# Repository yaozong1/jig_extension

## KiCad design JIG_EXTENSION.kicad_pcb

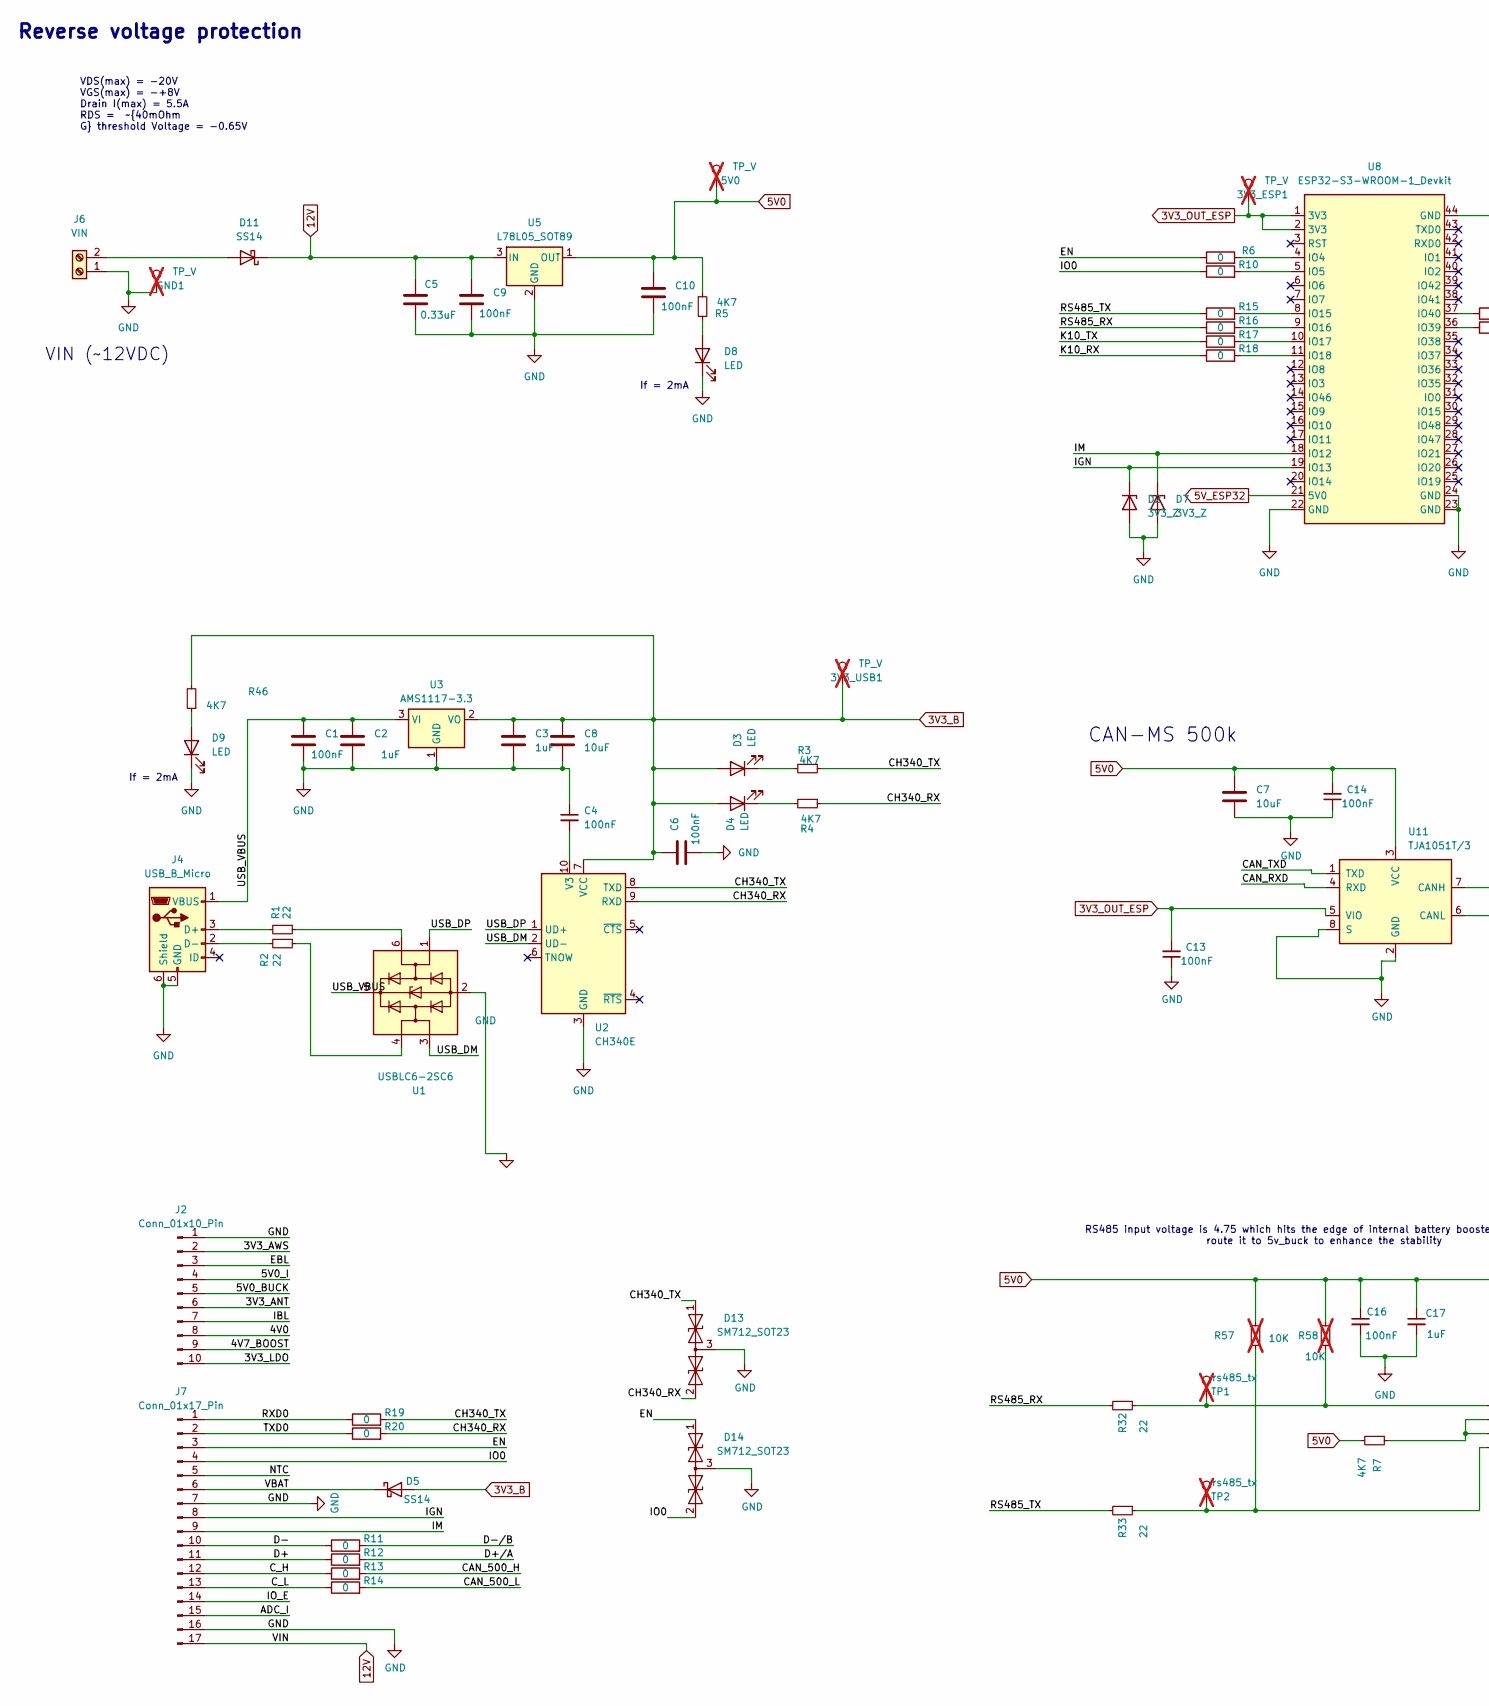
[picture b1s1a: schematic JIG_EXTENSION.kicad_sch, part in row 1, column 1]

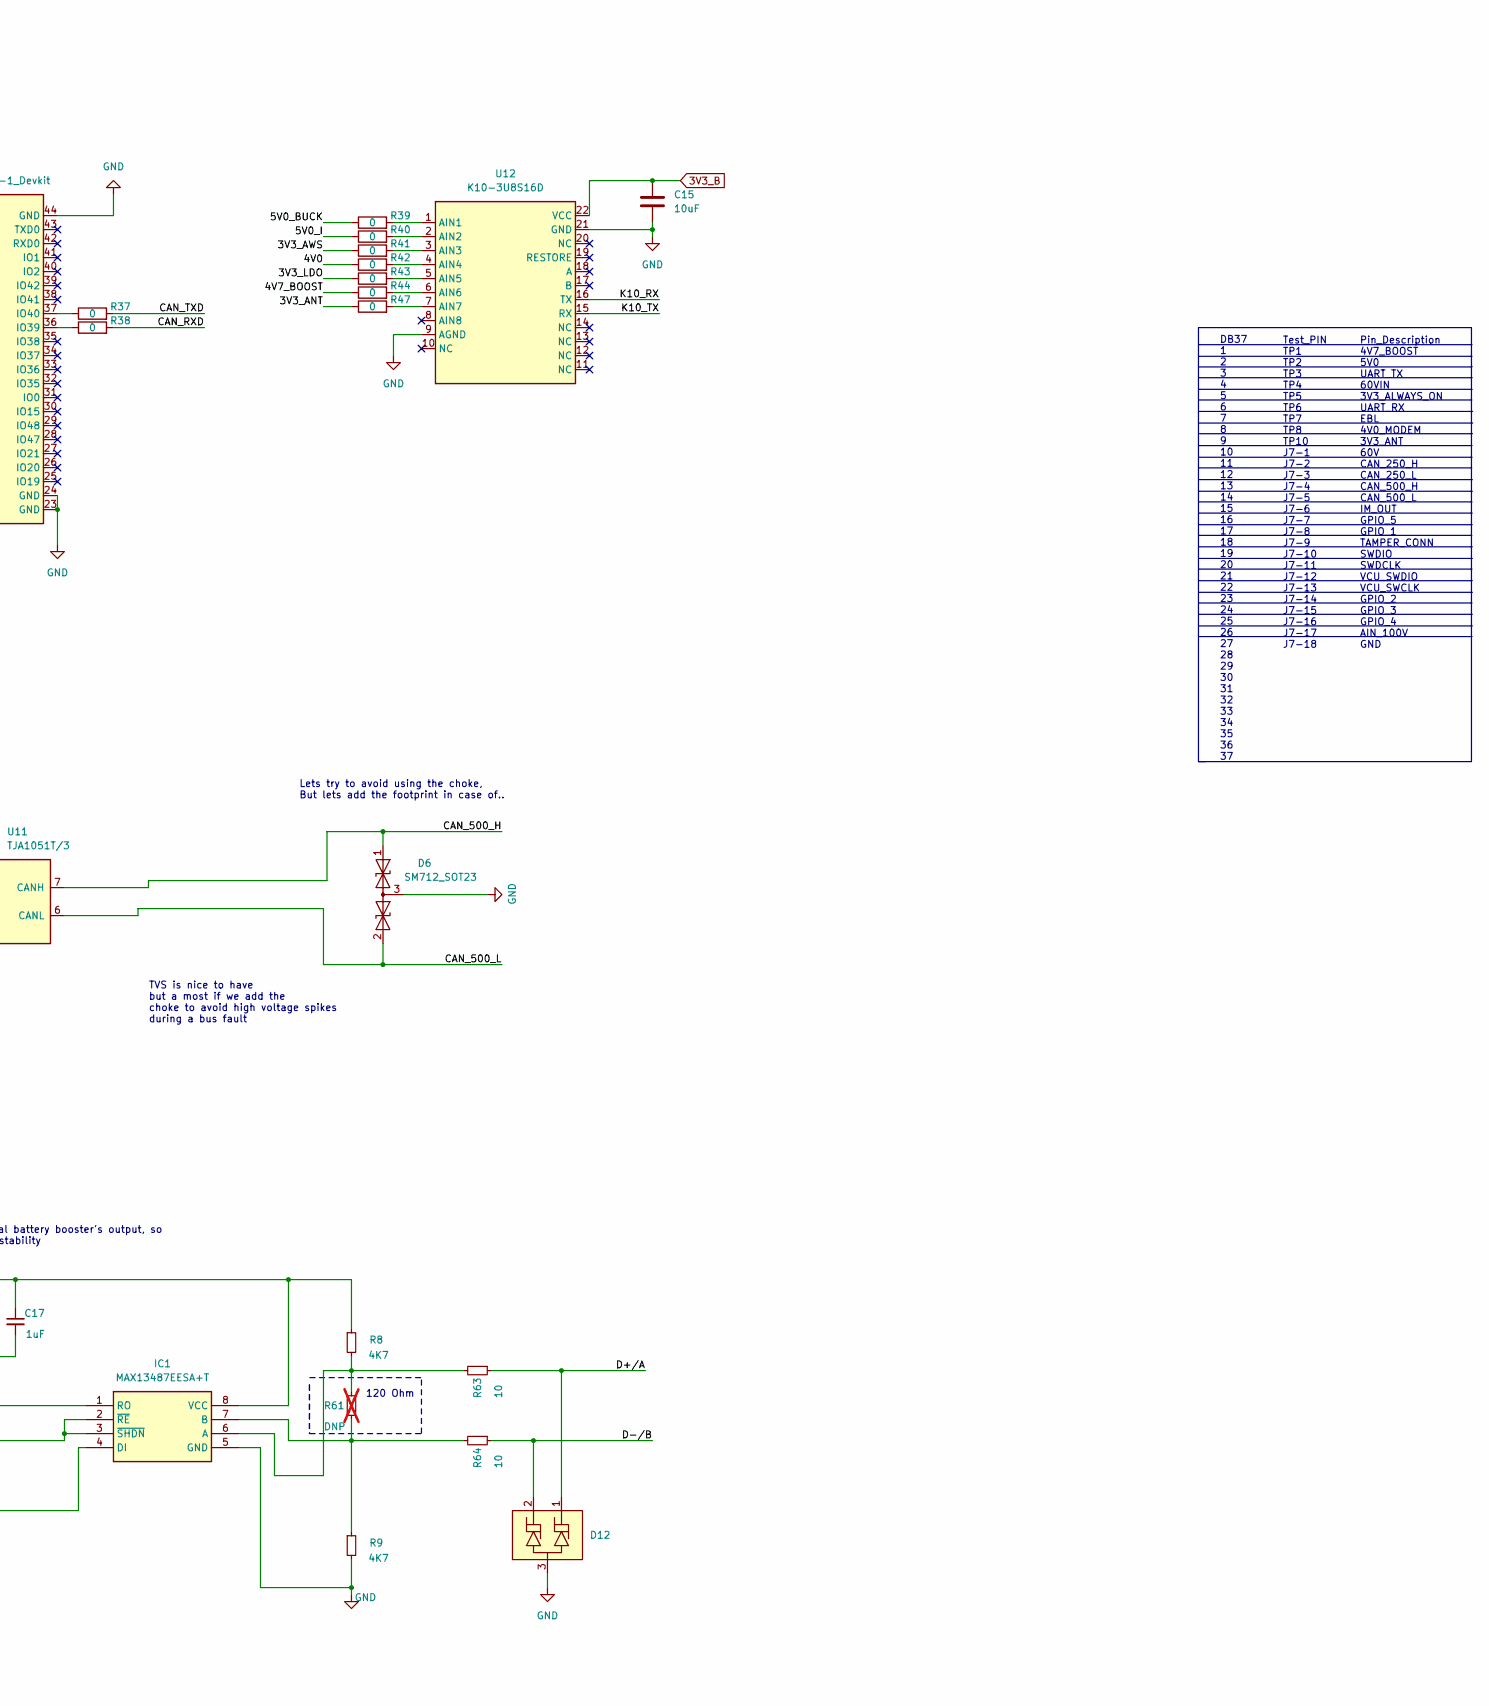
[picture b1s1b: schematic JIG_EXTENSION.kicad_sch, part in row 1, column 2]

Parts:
3V3_ESP1, 3V3_USB1, 5V0: TP_V; TestPoint_Pad_D1.0mm; MPN #N/A; LCSC Part #N/A; not fitted
C1, C4, C6, C9, C10, C13, C14, C16: 100nF; C_0603_1608Metric; MPN CC0603KRX7R9BB104; LCSC Part C14663
C2, C3, C17: 1uF; C_0603_1608Metric; MPN CL10A105KB8NNNC; LCSC Part C15849
C5: 0.33uF; C_0805_2012Metric; MPN 0805B334K500NT; LCSC Part C1740
C7, C8, C15: 10uF; C_0603_1608Metric; MPN CL10A106MA8NRNC; LCSC Part C96446
D2, D7: 3V3_Z; D_SOD-323; MPN BZT52C3V3S; LCSC Part C19077437
D3, D4, D8, D9: LED; LED_0603_1608Metric; MPN KT-0603R; LCSC Part C2286
D5, D11: SS14; D_SMA; MPN SS14; LCSC Part C2480
D6, D13, D14: SM712_SOT23; SOT-323_SC-70; MPN ESDCAN03-2BWY; LCSC Part C1973833
D12: PESD8V0L2BT-N; SOT-23; MPN PESD8V0L2BT-N; LCSC Part C316022
GND1: TP_V; TestPoint_Pad_D1.0mm; MPN #N/A; LCSC Part #N/A; not fitted
IC1: MAX13487EESA+T; SOIC127P600X175-8N; MPN MAX13487EESA+T; Mouser Part Number 700-MAX13487EESAT
J2: Conn_01x10_Pin; PinHeader_1x10_P2.54mm_Horizontal; MPN 2542WR-10P; LCSC Part C5383125
J4: USB_B_Micro; USB_Micro-B_Molex-105017-0001; MPN MicroXNJ; LCSC Part C404969
J6: VIN; TerminalBlock_Altech_AK300-2_P5.00mm; MPN WJ301V-5.0-02P-12-00A; LCSC Part C8475
J7: Conn_01x17_Pin; PinHeader_1x17_P2.54mm_Horizontal; MPN B-2100R17P-A110; LCSC Part C49423328
R1, R2, R32, R33: 22; R_0402_1005Metric; MPN 0402WGF220JTCE; LCSC Part C25092
R3, R4, R5, R7, R8, R9, R46: 4K7; R_0603_1608Metric; MPN 0603WAF4701T5E; LCSC Part C23162
R6, R10, R11, R12, R13, R14, R15, R16, R17, R18, R19, R20, R37, R38, R39, R40, R41, R42, R43, R44, R47: 0; R_0603_1608Metric; MPN 0603WAF0000T5E; LCSC Part C21189
R57, R58: 10K; R_0603_1608Metric; MPN 0603WAF1002T5E; LCSC Part C25804; not fitted
R61: DNP; R_0402_1005Metric; MPN #N/A; LCSC Part #N/A; not fitted
R63, R64: 10; R_0603_1608Metric; MPN 0603WAF100JT5E; LCSC Part C22859
TP1, TP2: rs485_tx; TestPoint_Pad_D1.0mm; MPN #N/A; LCSC Part #N/A; not fitted
U1: USBLC6-2SC6; SOT-23-6; MPN USBLC6-2SC6; LCSC Part C2827654
U2: CH340E; MSOP-10_3x3mm_P0.5mm; MPN CH340E; LCSC Part C99652
U3: AMS1117-3.3; SOT-223-3_TabPin2; MPN AMS1117-3.3; LCSC Part C6186
U5: L78L05_SOT89; SOT-89-3; MPN 78L05G-AB3-R; LCSC Part C71136
U8: ESP32-S3-WROOM-1_Devkit; ESP32S3_DevkitPinHeader_1x22_P2.54mm_Vertical; MPN BX-PM2.54-1-22PY; LCSC Part C18078140
U11: TJA1051T/3; SOIC-8_3.9x4.9mm_P1.27mm; MPN TJA1051T/3; LCSC Part C38695
U12: K10-3U8S16D; MPN PM2.0-1*12; LCSC Part C5307347

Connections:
3V3_B: 3V3_USB1.1, C3.1, C6.1, C8.1, C15.1, D3.2 (A), D4.2 (A), D5.2 (A), R46.2, U2.7 (VCC), U3.2 (VO), U12.22 (VCC)
3V3_OUT_ESP: 3V3_ESP1.1, C13.2, U8.1 (3V3), U8.2 (3V3), U11.5 (VIO)
5V0: 5V0.1, C7.1, C10.1, C14.2, C16.1, C17.1, IC1.8 (VCC), R5.1, R7.2, R8.1, R57.2, R58.2, U5.1 (OUT), U11.3 (VCC)
5V_ESP32: U8.21 (5V0)
12V: C5.1, C9.1, D11.1 (K), J7.17, U5.3 (IN)
/3V3_ANT: J2.6, R47.1
/3V3_AWS: J2.2, R41.1
/3V3_LDO: J2.10, R43.1
/4V0: J2.8, R42.1
/4V7_BOOST: J2.9, R44.1
/5V0_BUCK: J2.5, R39.1
/5V0_I: J2.4, R40.1
/ADC_I: J7.15
/CAN_500_H: D6.1 (A1), R13.2, U11.7 (CANH)
/CAN_500_L: D6.2 (A2), R14.2, U11.6 (CANL)
/CAN_RXD: R38.2, U11.4 (RXD)
/CAN_TXD: R37.2, U11.1 (TXD)
/CH340_RX: D13.2 (A2), R4.1, R20.2, U2.9 (RXD)
/CH340_TX: D13.1 (A1), R3.1, R19.2, U2.8 (TXD)
/C_H: J7.12, R13.1
/C_L: J7.13, R14.1
/D+: J7.11, R12.1
/D+/A: D12.1 (A1), R12.2, R63.1
/D-: J7.10, R11.1
/D-/B: D12.2 (A2), R11.2, R64.1
/EBL: J2.3
/EN: D14.1 (A1), J7.3, R6.1
/IBL: J2.7
/IGN: D2.1 (K), J7.8, U8.19 (IO13)
/IM: D7.1 (K), J7.9, U8.18 (IO12)
/IO0: D14.2 (A2), J7.4, R10.1
/IO_E: J7.14
/K10_RX: R18.1, U12.16 (TX)
/K10_TX: R17.1, U12.15 (RX)
/NTC: J7.5
/RS485_RX: R16.1, R32.2
/RS485_TX: R15.1, R33.2
/RXD0: J7.1, R19.1
/TXD0: J7.2, R20.1
/USB_DM: U1.3 (I/O2), U2.2 (UD-)
/USB_DP: U1.1 (I/O1), U2.1 (UD+)
/USB_VBUS: C1.1, C2.1, J4.1 (VBUS), U1.5 (VBUS), U3.3 (VI)
/VBAT: D5.1 (K), J7.6
GND: C1.2, C2.2, C3.2, C4.1, C5.2, C6.2, C7.2, C8.2, C9.2, C10.2, C13.1, C14.1, C15.2, C16.2, C17.2, D2.2 (A), D6.3 (common), D7.2 (A), D8.1 (K), D9.1 (K), D12.3 (A3), D13.3 (common), D14.3 (common), GND1.1, IC1.5 (GND), J2.1, J4.5 (GND), J4.6 (Shield), J6.1, J7.7, J7.16, R9.2, U1.2 (GND), U2.3 (GND), U3.1 (GND), U5.2 (GND), U8.22 (GND), U8.23 (GND), U8.24 (GND), U8.44 (GND), U11.2 (GND), U11.8 (S), U12.9 (AGND), U12.21 (GND)
unnamed: D3.1 (K), R3.2
unnamed: D4.1 (K), R4.2
unnamed: D8.2 (A), R5.2
unnamed: D9.2 (A), R46.1
unnamed: D11.2 (A), J6.2
unnamed: IC1.6 (A), R8.2, R61.2, R63.2
unnamed: IC1.7 (B), R9.1, R61.1, R64.2
unnamed: IC1.4 (DI), R33.1, R57.1, TP2.1
unnamed: IC1.1 (RO), R32.1, R58.1, TP1.1
unnamed: IC1.2 (~RE), IC1.3 (~SHDN), R7.1
unnamed: J4.3 (D+), R1.2
unnamed: J4.2 (D-), R2.2
unnamed: R1.1, U1.6 (I/O1)
unnamed: R2.1, U1.4 (I/O2)
unnamed: R15.2, U8.8 (IO15)
unnamed: C4.2, U2.10 (V3)
unnamed: R6.2, U8.4 (IO4)
unnamed: R10.2, U8.5 (IO5)
unnamed: R16.2, U8.9 (IO16)
unnamed: R17.2, U8.10 (IO17)
unnamed: R18.2, U8.11 (IO18)
unnamed: R38.1, U8.36 (IO39)
unnamed: R37.1, U8.37 (IO40)
unnamed: R39.2, U12.1 (AIN1)
unnamed: R40.2, U12.2 (AIN2)
unnamed: R41.2, U12.3 (AIN3)
unnamed: R42.2, U12.4 (AIN4)
unnamed: R43.2, U12.5 (AIN5)
unnamed: R44.2, U12.6 (AIN6)
unnamed: R47.2, U12.7 (AIN7)

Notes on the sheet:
If = 2mA
CAN-MS 500k
Test_PIN TP1 TP2 TP3 TP4 TP5 TP6 TP7 TP8 TP10 J7-1 J7-2 J7-3 J7-4 J7-5 J7-6 J7-7 J7-8 J7-9 J7-10 J7-11 J7-12 J7-13 J7-14 J7-15 J7-16 J7-17 J7-18
120 Ohm
RS485 input voltage is 4.75 which hits the edge of internal battery booster's output, so route it to 5v_buck to enhance the stability
TVS is nice to have but a most if we add the choke to avoid high voltage spikes during a bus fault
VDS(max) = -20V VGS(max) = -+8V Drain I(max) = 5.5A RDS = ~{40mOhm G} threshold Voltage = -0.65V
Reverse voltage protection
Pin_Description 4V7_BOOST 5V0 UART_TX 60VIN 3V3_ALWAYS_ON UART_RX EBL 4V0_MODEM 3V3_ANT 60V CAN_250_H CAN_250_L CAN_500_H CAN_500_L IM_OUT GPIO_5 GPIO_1 TAMPER_CONN SWDIO SWDCLK VCU_SWDIO VCU_SWCLK GPIO_2 GPIO_3 GPIO_4 AIN_100V GND
Lets try to avoid using the choke, But lets add the footprint in case of..
VIN (~12VDC)
DB37 1 2 3 4 5 6 7 8 9 10 11 12 13 14 15 16 17 18 19 20 21 22 23 24 25 26 27 28 29 30 31 32 33 34 35 36 37

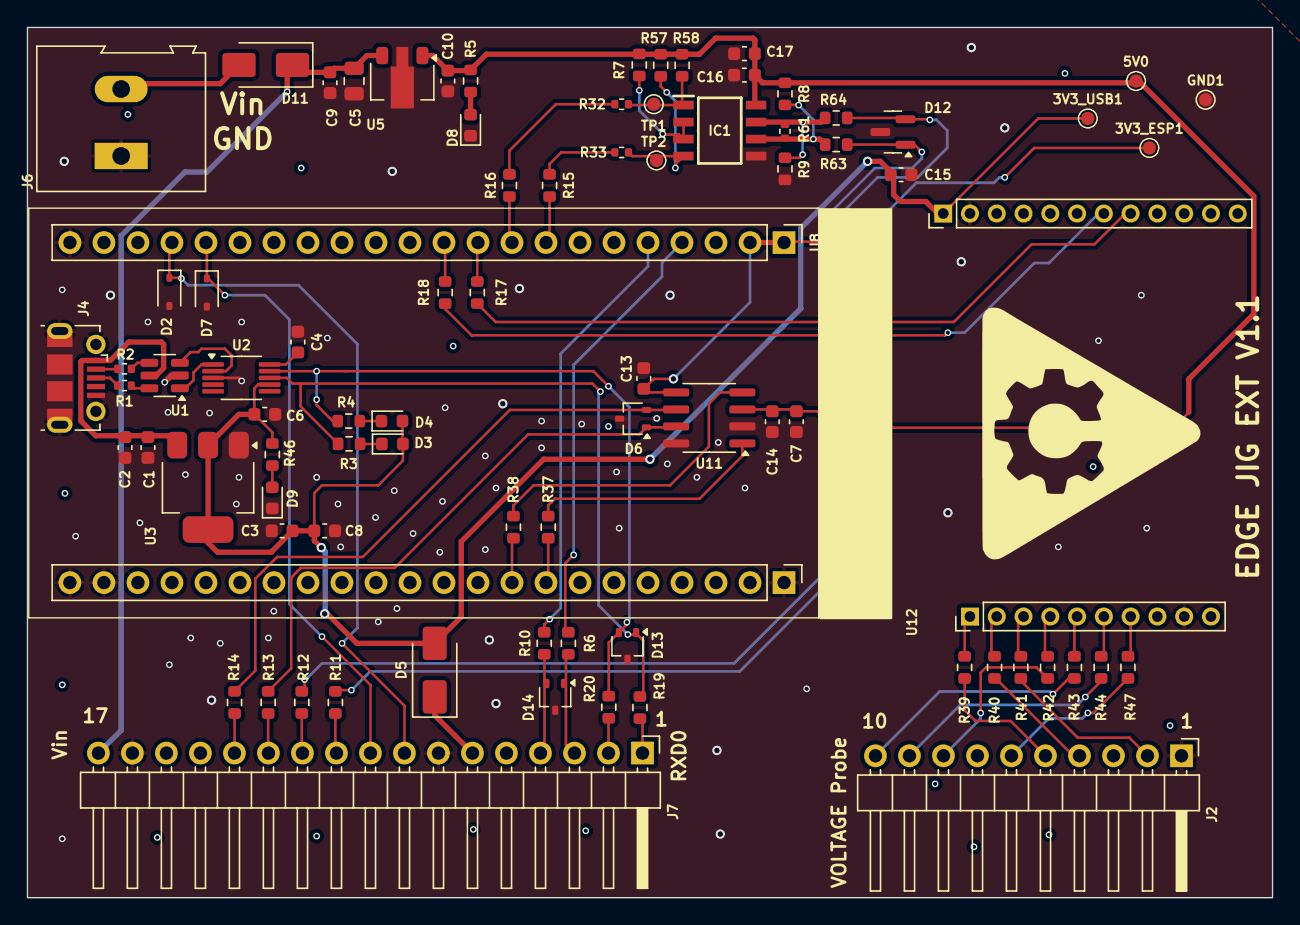
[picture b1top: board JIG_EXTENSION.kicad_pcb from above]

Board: 2 copper layers, 93.0 x 65.0 mm, 82 parts (0 on the bottom side), 68 nets.

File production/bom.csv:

Designator,Footprint,Quantity,Value,LCSC Part #
"C1, C10, C13, C14, C16, C4, C6, C9",0603,8,100nF,C14663
"C15, C7, C8",0603,3,10uF,C96446
"C17, C2, C3",0603,3,1uF,C15849
C5,0805,1,0.33uF,C1740
"D11, D5",D_SMA,2,SS14,C2480
D12,SOT-23,1,PESD8V0L2BT-N,C316022
"D13, D14, D6",SOT-323_SC-70,3,SM712_SOT23,C1973833
"D2, D7",D_SOD-323,2,3V3_Z,C19077437
"D3, D4, D8, D9",0603,4,LED,C2286
IC1,SOIC127P600X175-8N,1,MAX13487EESA+T,C18347
J2,PinHeader_1x10_P2.54mm_Horizontal,1,Conn_01x10_Pin,C5383125
J4,USB_Micro-B_Molex-105017-0001,1,USB_B_Micro,C404969
J6,TerminalBlock_Altech_AK300-2_P5.00mm,1,VIN,C8475
J7,PinHeader_1x17_P2.54mm_Horizontal,1,Conn_01x17_Pin,C49423328
"R1, R2, R32, R33",0402,4,22,C25092
"R10, R11, R12, R13, R14, R15, R16, R17, R18, R19, R20, R37, R38, R39, R40, R41, R42, R43, R44, R47, R6",0603,21,0,C21189
"R3, R4, R46, R5, R7, R8, R9",0603,7,4K7,C23162
"R57, R58",0603,2,10K,C25804
"R63, R64",0603,2,10,C22859
U1,SOT-23-6,1,USBLC6-2SC6,C2827654
U11,SOIC-8_3.9x4.9mm_P1.27mm,1,TJA1051T/3,C38695
U12,K10-3U8S16D,1,K10-3U8S16D,C5307347
U2,MSOP-10_3x3mm_P0.5mm,1,CH340E,C99652
U3,SOT-223-3_TabPin2,1,AMS1117-3.3,C6186
U5,SOT-89-3,1,L78L05_SOT89,C71136
U8,ESP32S3_DevkitPinHeader_1x22_P2.54mm_Vertical,1,ESP32-S3-WROOM-1_Devkit,C18078140

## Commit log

2023-07-13 ready to produce
2024-01-26 saveddddd
2024-02-27 update lib only
2024-02-27 keep track of lastest lib
2024-02-29 UPDATE BOM
2025-12-27 done
2026-01-06 modified 5V0
2026-01-07 added note on sch for 3v3_B
